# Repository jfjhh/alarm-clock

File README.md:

# Alarm Clock

KiCad and related files for a simple alarm clock project.

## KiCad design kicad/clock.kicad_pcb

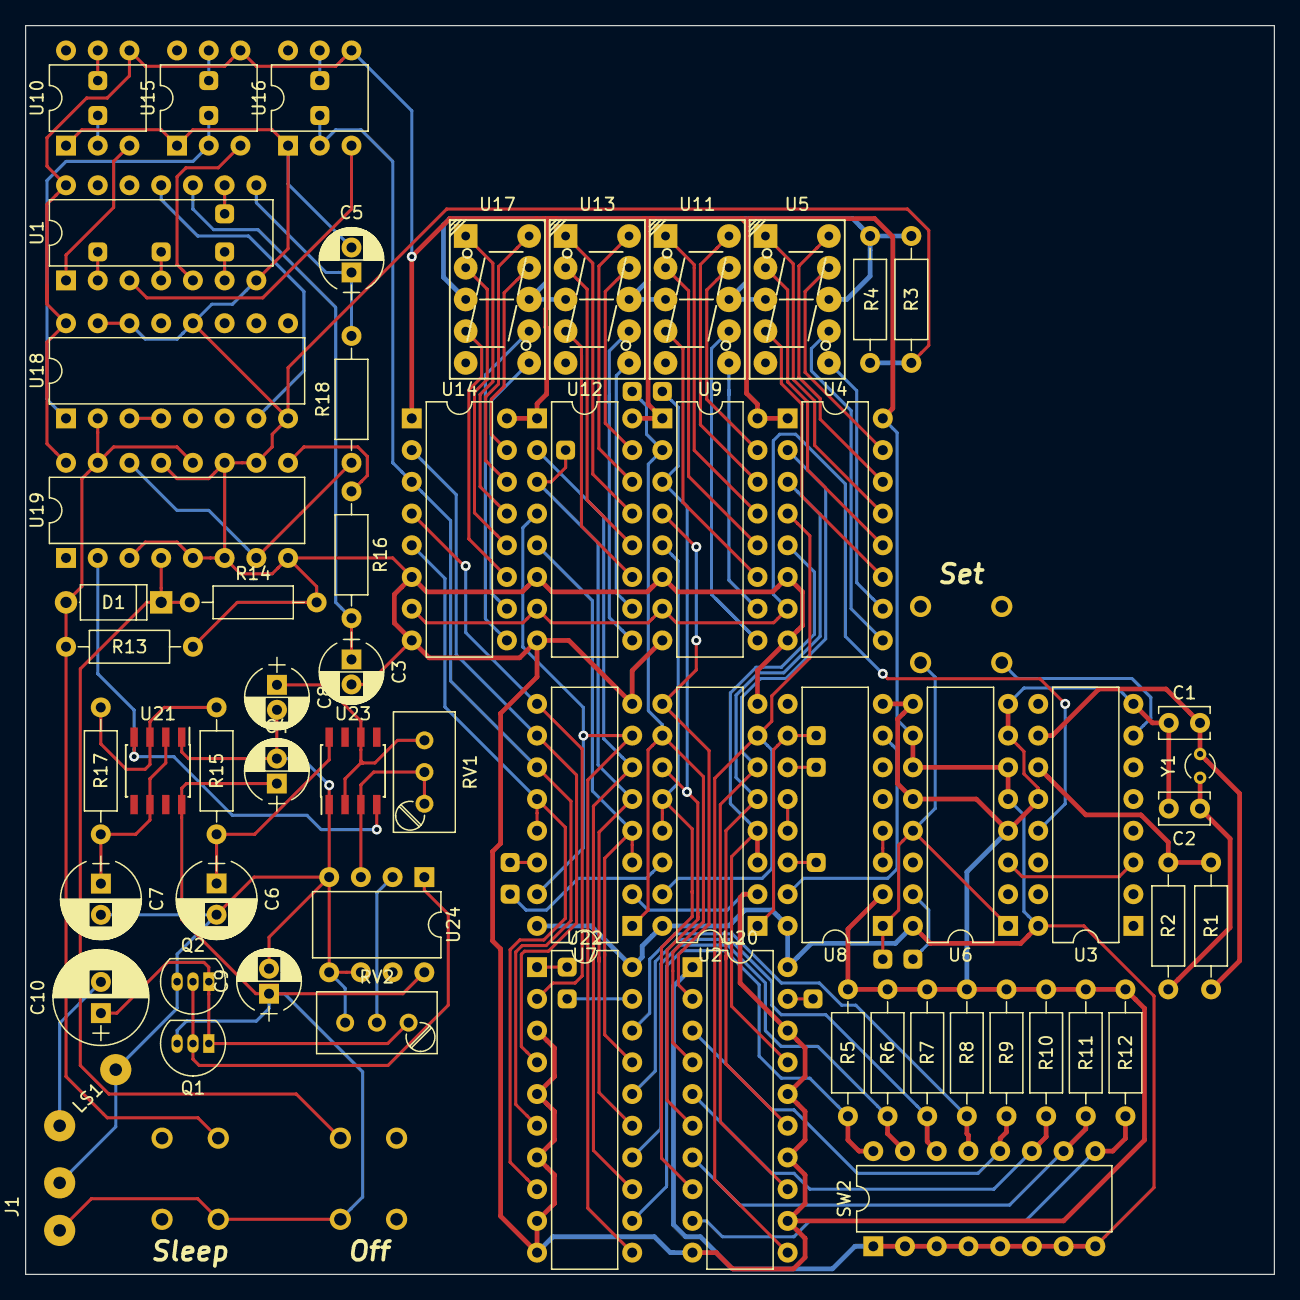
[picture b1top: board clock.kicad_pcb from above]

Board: 4 copper layers, 100.0 x 100.0 mm, 87 parts (1 on the bottom side), 94 nets.

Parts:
C1, C2: 33p; C_Rect_L4.0mm_W2.5mm_P2.50mm
C3, C4, C5, C8, C9: 0u1; CP_Radial_D5.0mm_P2.00mm
C6, C7: 10u; CP_Radial_D6.3mm_P2.50mm
C10: 100u; CP_Radial_D7.5mm_P2.50mm
D1: D_Schottky_ALT; D_A-405_P7.62mm_Horizontal
J1: Conn_01x02_Female; SolderWirePad_2x_1mmDrill
LS1: Beep; WireConnection_1.00mmDrill
Q1: PN2222A; TO-92_Inline_Narrow_Oval
Q2: 2N3906; TO-92_Inline_Narrow_Oval
R1: 10M; R_Axial_DIN0207_L6.3mm_D2.5mm_P10.16mm_Horizontal
R2, R17: 100k; R_Axial_DIN0207_L6.3mm_D2.5mm_P10.16mm_Horizontal
R3, R4, R15: 1k; R_Axial_DIN0207_L6.3mm_D2.5mm_P10.16mm_Horizontal
R5, R6, R7, R8, R9, R10, R11, R12, R13, R14: 22k; R_Axial_DIN0207_L6.3mm_D2.5mm_P10.16mm_Horizontal
R16, R18: 47R; R_Axial_DIN0207_L6.3mm_D2.5mm_P10.16mm_Horizontal
RV1: 50k; Potentiometer_Trimmer_Bourns_3296W
RV2: 10k; Potentiometer_Trimmer_Bourns_3296W
SW1, SW3, SW4: SW_Push; SW_TH_Tactile_Omron_B3F-10xx
SW2: SW_DIP_x08; DIP-16_W7.62mm
TP1, TP1#2, TP1#3, TP1#4, TP1#5, TP1#6, TP1#7, TP1#8, TP1#9, TP1#10, TP1#11, TP1#12, TP1#13, TP1#14, TP1#15, TP1#16, TP1#17, TP1#18, TP1#19, TP1#20, TP1#21, TP1#22, TP1#23: 0.5 Hz; TestPoint
U1: 74HC04; DIP-14_W7.62mm
U2, U7, U8, U18: 74LS390; DIP-16_W7.62mm
U3: CD4060; DIP-16_W7.62mm
U4, U9, U12, U14: 4543; DIP-16_W7.62mm
U5, U11, U13, U17: 7SEGMENT_CC; HDSP-78xx
U6, U19: 4027; DIP-16_W7.62mm
U10, U15, U16: Discrete_NAND; DIP-6_W7.62mm
U20, U22: 74HC688; DIP-20_W7.62mm
U21, U23: TLC555CD; SOIC-8_3.9x4.9mm_Pitch1.27mm
U24: LM358; DIP-8_W7.62mm
Y1: 32768; Crystal_DS26_d2.0mm_l6.0mm_Vertical

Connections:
0.5Hz: TP1.1, TP1#2.1, TP1#3.1, TP1#4.1, TP1#5.1, TP1#6.1, TP1#7.1, TP1#8.1, TP1#9.1, TP1#10.1, TP1#11.1, TP1#12.1, TP1#13.1, TP1#14.1, TP1#15.1, TP1#16.1, TP1#17.1, TP1#18.1, TP1#19.1, TP1#20.1, TP1#21.1, TP1#22.1, TP1#23.1, U6.15
1Hz: SW1.2, U6.1, U6.13, U8.1
1hr: U2.10, U7.1, U9.2, U10.2, U20.4
1min: U2.1, U8.10, U15.2, U18.1
/Alarm/B0: R5.2, SW2.16, U22.12
/Alarm/B1: R6.2, SW2.15, U22.14
/Alarm/B2: R7.2, SW2.14, U22.16
/Alarm/B3: R8.2, SW2.13, U22.18
/Alarm/B4: R9.2, SW2.12, U20.3
/Alarm/B5: R10.2, SW2.11, U20.5
/Alarm/B6: R11.2, SW2.10, U20.7
/Alarm/B7: R12.2, SW2.9, U20.9
ALM: R18.1, U19.7, U19.14
GND: C1.2, C2.2, C3.2, C4.2, C5.2, C6.2, C7.2, C8.2, C9.2, J1.2, LS1.2, Q2.3, R3.2, R4.2, R5.1, R6.1, R7.1, R8.1, R9.1, R10.1, R11.1, R12.1, R13.2, R14.2, RV2.3, U1.7, U2.2, U2.8, U3.8, U3.12, U4.6, U4.8, U6.4, U6.7, U6.8, U6.9, U6.12, U7.2, U7.8, U8.2, U8.8, U9.6, U9.8, U10.1, U12.6, U12.8, U14.6, U14.8, U15.1, U16.1, U18.8, U18.12, U18.14, U18.15, U19.3, U19.5, U19.6, U19.8, U19.10, U19.11, U19.13, U20.10, U20.12, U20.14, U20.16, U20.18, U21.1, U22.3, U22.5, U22.7, U22.9, U22.10, U23.1, U24.4, U24.5, U24.6
HH0: U7.12, U7.13, U14.5, U22.8
HH1: U7.11, U14.3, U16.2, U22.6
HH2: U7.10, U14.2, U22.4
HH3: U7.9, U14.4, U22.2
HL0: U7.3, U7.4, U12.5, U22.17
HL1: U7.5, U12.3, U16.5, U22.15
HL2: U7.6, U12.2, U22.13
HL3: U7.7, U7.15, U12.4, U22.11
MH0: U2.12, U2.13, U9.5, U20.8
MH1: U2.11, U9.3, U10.5, U20.6
MH3: U2.9, U9.4, U20.2
ML0: U2.3, U2.4, U4.5, U20.17
ML1: U2.5, U4.3, U20.15
ML2: U2.6, U4.2, U20.13
ML3: U2.7, U2.15, U4.4, U20.11
unnamed: C1.1, R1.2, U3.10, Y1.1
unnamed: C2.1, R2.2, Y1.2
unnamed: C3.1, R16.2, U1.10
unnamed: C5.1, R18.2, U1.8
unnamed: C6.1, R15.1, U23.8
unnamed: C7.1, R17.2, U21.2, U21.6
unnamed: C8.1, RV1.3, U23.2, U23.6
unnamed: C10.1, Q1.1, Q2.1, RV2.1
unnamed: C10.2, LS1.1
unnamed: D1.2, R13.1, SW3.2, U18.2, U19.12, U19.15
unnamed: Q1.2, Q2.2, U24.1
unnamed: R1.1, R2.1, U3.11
unnamed: R3.1, R4.1, U5.3, U5.8, U11.3, U11.8, U13.3, U13.8, U17.3, U17.8
unnamed: R15.2, R17.1, U21.3
unnamed: R16.1, U19.9
unnamed: RV1.1, RV1.2, U23.3, U24.3
unnamed: RV2.2, U24.2
unnamed: SW1.1, U3.7
unnamed: U1.1, U10.3
unnamed: U1.2, U2.14
unnamed: U1.3, U16.3
unnamed: U1.4, U7.14
unnamed: U1.5, U15.3
unnamed: U1.6, U8.14
unnamed: U1.9, U22.19
unnamed: U1.11, U18.7
unnamed: U3.3, U6.3
unnamed: U4.9, U5.7
unnamed: U4.10, U5.6
unnamed: U4.11, U5.4
unnamed: U4.12, U5.2
unnamed: U4.13, U5.1
unnamed: U4.14, U5.10
unnamed: U4.15, U5.9
unnamed: U8.3, U8.4
unnamed: U8.12, U8.13
unnamed: U8.7, U8.15
unnamed: U9.13, U11.1
unnamed: U9.12, U11.2
unnamed: U9.11, U11.4
unnamed: U9.10, U11.6
unnamed: U9.9, U11.7
unnamed: U9.15, U11.9
unnamed: U9.14, U11.10
unnamed: U12.9, U13.7
unnamed: U12.10, U13.6
unnamed: U12.11, U13.4
unnamed: U12.12, U13.2
unnamed: U12.13, U13.1
unnamed: U12.14, U13.10
unnamed: U12.15, U13.9
unnamed: U14.9, U17.7
unnamed: U14.10, U17.6
unnamed: U14.11, U17.4
unnamed: U14.12, U17.2
unnamed: U14.13, U17.1
unnamed: U14.14, U17.10
unnamed: U14.15, U17.9
unnamed: U8.11, U15.5
unnamed: U18.3, U18.4
unnamed: U20.19, U22.1
OFF: D1.1, R14.1, SW4.2, U19.4
PWM: U3.13, U4.7, U9.7, U12.7, U14.7
VCC: C4.1, C9.1, J1.1, Q1.3, SW2.1, SW2.2, SW2.3, SW2.4, SW2.5, SW2.6, SW2.7, SW2.8, SW3.1, SW4.1, U1.14, U2.16, U3.16, U4.1, U4.16, U6.5, U6.6, U6.10, U6.11, U6.16, U7.16, U8.16, U9.1, U9.16, U10.4, U12.1, U12.16, U14.1, U14.16, U15.4, U16.4, U18.16, U19.16, U20.1, U20.20, U21.8, U22.20, U24.8
~BEEP: U19.2, U21.4, U23.4

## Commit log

2019-05-30 Init
2019-05-31 Finished rough schematic
2019-07-20 Fixed and prettied schematic
2019-07-20 Some grouping
2019-07-20 Fixed buses between sheets; comparator BCD inputs connected
2019-07-21 Now how to route the BCD buses?
2019-07-28 One 7-seg display routed
2019-07-28 BCD output bus available
2019-07-28 More routing, but oops displays are backwards and it's all for nothing
2019-08-03 Routed switches
2019-08-04 Corrected schematic: SET button and discrete NAND blob
2019-09-02 All but beep routing done
2019-09-09 New beeping circuit
2019-09-09 Beep circuit mostly routed
2019-09-10 Routing done: need board edges
